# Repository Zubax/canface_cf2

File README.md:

# Babel-Babel

All-in-one hardware solution for developing [Cyphal/CAN](https://opencyphal.org) and DroneCAN devices.

Babel-Babel consists of three devices that are assembled on a single PCB:
2x [Babel](https://zubax.com/babel) USB-CAN adapters and a
[Dronecode probe](https://shop.zubax.com/collections/development-tools/products/dronecode-probe-v2-2-jtag-swd-adapter-usb-uart-adapter-with-dcd-m-cable)
(a generic JTAG/SWD + UART console adapter).

Babel-Babel is connected to the PC with a single USB cable as it contains a built-in USB hub.
It provides the following interfaces for connecting to the device under development:

- CAN 1 (UCANPHY Micro connector)
- CAN 2 (UCANPHY Micro connector)
- SWD and UART (Dronecode Debug connector, medium)
- USB (regular USB A connector)

Along with that, all these interfaces are routed to additional PLS connectors (regular 0.1' single-row pin headers).
These connectors may be used for production testing purposes.

Each Babel can be turned off using the corresponding dip switch.

For technical characteristics, please refer to [requirements document](/docs/requirements.md).

## Standalone debug tool

When the device is used as a standalone debug tool (when the pin headers are not used),
Babel-Babel is constructed using a "novel approach" often called oreo-construction.
This approach eliminates the need for having separate housing,
reliably protecting all the electronics inside the device
while also providing a possibility to deposit some explanatory notes on the top surface of the device
(like the purpose of connectors, pinouts, etc.) without any additional technological processes,
which allows Babel-Babel to be a relatively self-documenting device.

## Production flashing tool

To use Babel-Babel as a production flashing and testing tool, an adapter PCB should be designed.
In general, such PCB should have PBS connectors for Babel-Babel on one side and some connectors
for the device under test (usually pogo pins).
Both Babel-Babel and the device under test can then be connected to this adapter PCB and
the flashing and testing routine can be performed.

Although using Babel-Babel for testing requires some preparations,
it still may be beneficial as it greatly reduces the total amount of
wiring and connectors involved in the production testing routine.
This, in turn, makes the process faster, more reliable, and less painstaking.

The [Mitochondrik-LV](https://zubax.com/mitochondrik-lv) evaluation board is a good example.
To eliminate additional adapter PCBs, the evaluation board is designed to host Babel-Babel directly:

## Manufacturing instructions

For details on the manufacturing process of the device, check the
instructions at [manufacturing document](/docs/manufacturing.md).

## Release notes

Newest entries at the top.

### v1.3 (2025)

* Flip the two rest switches.
* Replaced obsolete part:

| Original | Alternative |
| -------- | ----------- |
| NS5B1G385DTT1G | 74AHC1G66GV,125 |

### v1.2.2 (2023)

* Added alternative part:

| Original | Alternative |
| -------- | ----------- |
| 74LVC2T45DC,125 | 74LVC2T45DC-Q100H |

### v1.2.1 (2023)

* Replaced Parts A, C, and D (spacer) PCBs with 3D.
* Added the Zubax logo to the enclosure PCB.

### v1.2 (2023)

* Fixed silkscreen labels and BOM inconsistencies.
* Replaced references to UAVCAN with Cyphal/CAN.

### v1.1 (2023)

* CAN VDD pulled high with resistor.
* Bootloader switch added to DCP with added pulup resistor.
* CAN VBUS voltage measurement implemented.

### v1.0 (2021)

The original version.

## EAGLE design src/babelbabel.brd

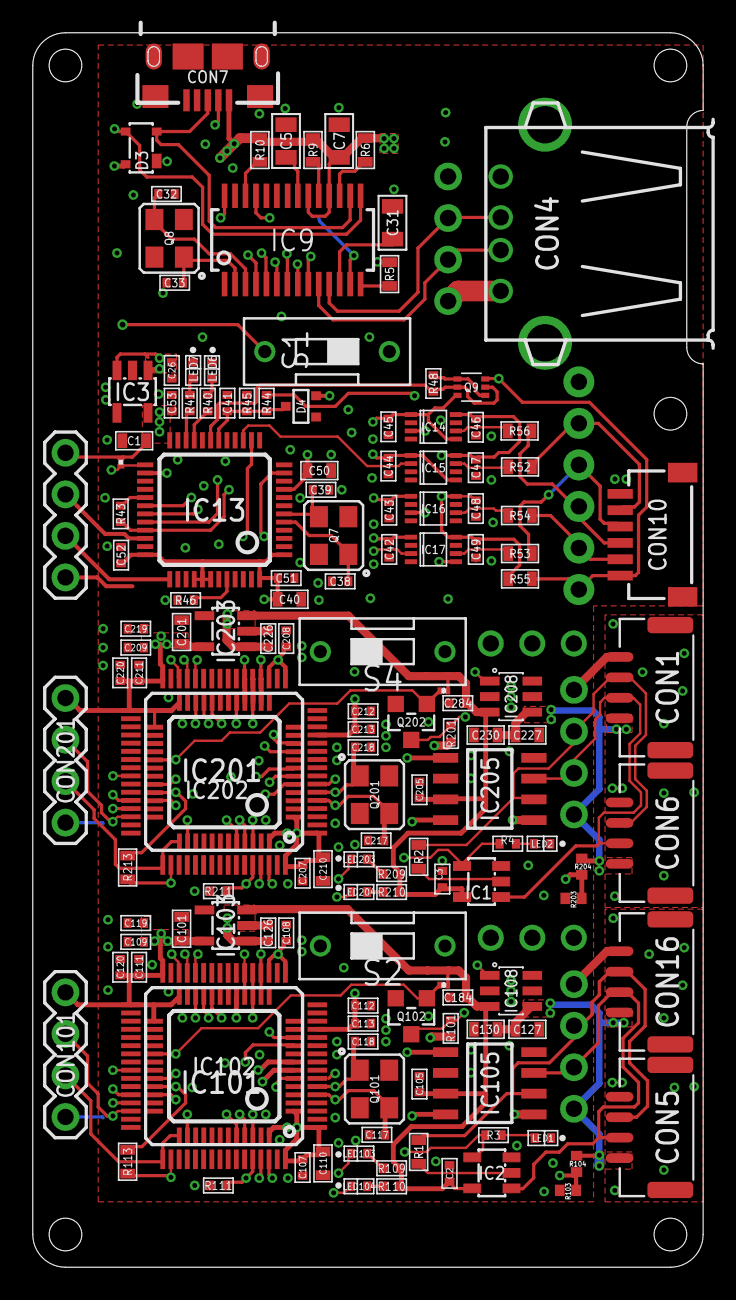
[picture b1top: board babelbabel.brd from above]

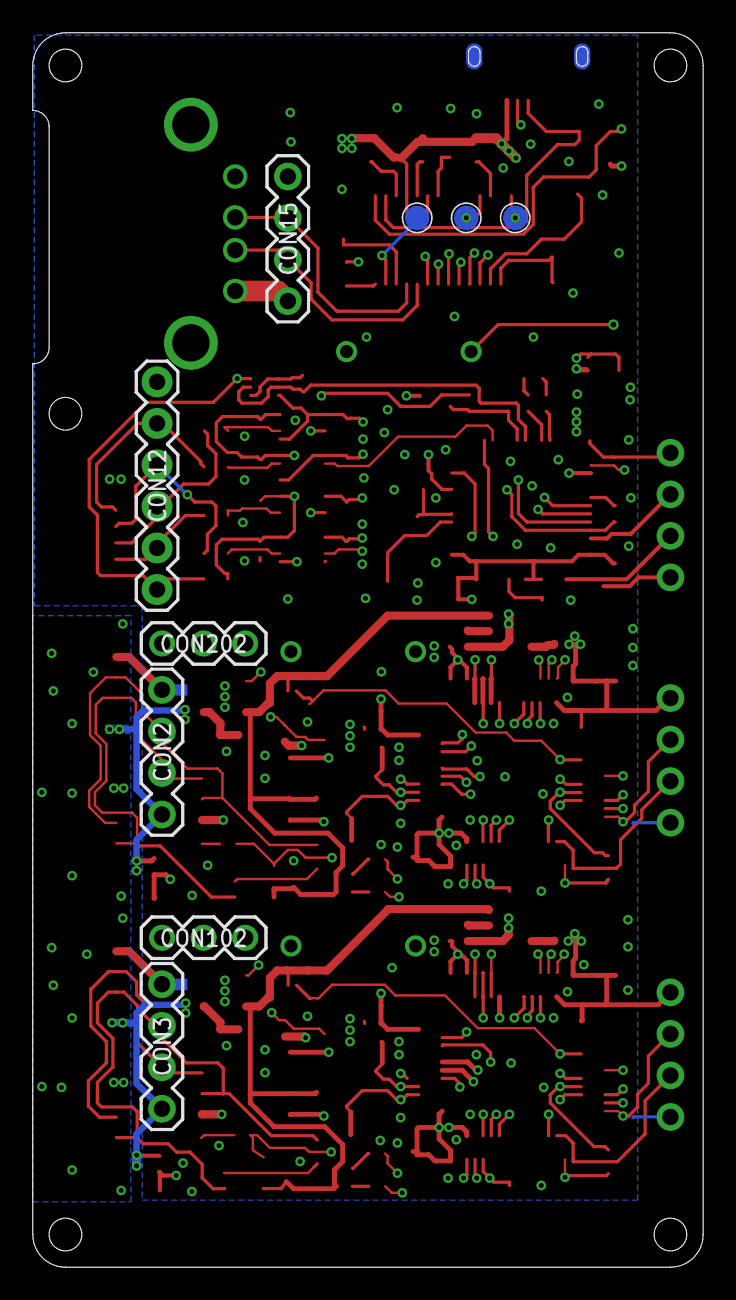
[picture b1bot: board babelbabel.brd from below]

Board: 4 copper layers, 41.0 x 75.5 mm, 156 parts (11 on the bottom side), 106 nets.

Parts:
C1, C40, C50, C101, C110, C127, C130, C201, C210, C227, C230: 4.7uF; C0603
C2, C3, C41, C42, C43, C44, C45, C46, C47, C48, C49, C51, C52, C53, C105, C107, C108, C184, C205, C207, C208, C284: 0.1uF; C0402
C5, C7, C31: 10uF; C0805
C26, C112, C119, C120, C126, C212, C219, C220, C226: 1uF; C0402
C32, C33, C117, C118, C217, C218: 20pF; C0402
C38, C39: 10pF; C0402
C109, C111, C113, C209, C211, C213: 10nF; C0402
CON1, CON5, CON6, CON16: CON-4P-TABS-JST_GH-RA; JST_GH-4P-RA
CON2, CON3, CON11, CON15, CON101, CON201: PINHEAD_1X04-2.54; 1X04-PTH-2.54
CON4: USB-AA-PTH; USB-A-F-PTH
CON7: USB-1; MICRO_USB_PEGS
CON10: CON-6P-SM06B; SM06B
CON12: PINHEAD_1X06-2.54; 1X06-PTH-2.54
CON102, CON202: PINHEAD_1X03-2.54; 1X03-PTH-2.54
D3: PRTR5V0U2X; SOT143B
D4: BAT54SWT1G; SC70
IC1, IC2: NS5B1G385; SOT23-5L
IC3, IC103, IC203: AP2127-3.3; SOT23-5
IC9: FE1.1S; SSOP-28
IC13: STM32F103CBT7; LQFP48
IC14, IC15, IC16, IC17: 74LVC2T45; VSSOP8
IC101, IC201: STM32F373CBT6-LQFP48; LQFP48
IC102, IC202: STM32F373RCT6; TQFP64
IC105, IC205: TJA1051-SO8; SOIC8
IC108, IC208: TPD3S014DBVR-SOT23-6; SOT26
J1, J2: CONNECTION-SMD; CONNECTION
LED1, LED2, LED6, LED7, LED103, LED104, LED203, LED204: LED-0402; LED0402
PAD1, PAD2, PAD4: PAD-S_2X2; 2х2
Q7: 8MHz; OSCILLATOR-3.2X2.5-4P
Q8: 12MHz; OSCILLATOR-3.2X2.5-4P
Q9: NTZD3152PT1G; SOT-563
Q101, Q201: 16MHz; OSCILLATOR-3.2X2.5-4P
Q102, Q202: 2N7002; SOT23
R1, R2, R52, R53, R54, R55, R56: 120R; R0603
R3, R4, R40, R41, R109, R110, R209, R210: 1K; R0402
R5: 2.7K; R0603
R6, R9, R10: 100K; R0603
R8, R102, R202: 10k; R0201
R43: 1K5; R0402
R44: 4K7; R0402
R45, R46, R48, R101, R111, R201, R211: 10K; R0402
R103, R104, R203, R204: 10k; R0402
R113, R213: 1K5; R0603
S1, S2, S4: DS01-STRAIGHT; DS-01

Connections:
BABEL1:BOOT0: IC101.44, IC102.60, R111.2
BABEL1:CAN_COMM: IC101.22, IC102.30, LED104.C
BABEL1:CAN_RX: IC101.45, IC102.61, IC105.4
BABEL1:CAN_STATUS: IC101.21, IC102.29, LED103.C
BABEL1:CAN_TX: IC101.46, IC102.62, IC105.1
BABEL1:CAN_VDD_EN: IC101.29, IC102.41, Q102.1, R102.1
BABEL1:N$1: IC108.1, Q102.3, R101.1
BABEL1:N$4: IC101.10, R103.1, R104.2
BABEL1:N$27: LED103.A, R109.1
BABEL1:N$28: LED104.A, R110.1
BABEL1:PA4: CON102.3, IC101.14, IC102.20
BABEL1:PA5: CON102.2, IC101.15, IC102.21
BABEL1:PA6: CON102.1, IC101.16, IC102.22
BABEL1:PF0: C117.2, IC101.5, IC102.5, Q101.3
BABEL1:PF1: C118.2, IC101.6, IC102.6, Q101.1
BABEL1:SWCLK: CON101.2, IC101.37, IC102.49
BABEL1:SWDIO: CON101.3, IC101.34, IC102.46
BABEL1:USB_PU: IC101.38, IC102.50, R113.2
BABEL1:VDD_3V3: C101.2, C107.1, C108.1, C109.2, C110.1, C111.2, C112.2, C113.2, C119.2, C120.2, CON101.4, IC101.1, IC101.9, IC101.17, IC101.24, IC101.25, IC101.48, IC102.1, IC102.13, IC102.17, IC102.19, IC102.32, IC102.33, IC102.64, IC103.5, IC105.5, R101.2
BABEL1_RST: IC101.7, IC102.7, S2.1
BABEL1_RST1: IC201.7, IC202.7, S4.1
BABEL1_TERM: IC2.4, IC101.20, IC102.28, R3.2
BABEL1_USB_N: IC9.4, IC101.32, IC102.44
BABEL1_USB_P: IC9.5, IC101.33, IC102.45, R113.1
BABEL2:BOOT0: IC201.44, IC202.60, R211.2
BABEL2:CAN_COMM: IC201.22, IC202.30, LED204.C
BABEL2:CAN_RX: IC201.45, IC202.61, IC205.4
BABEL2:CAN_STATUS: IC201.21, IC202.29, LED203.C
BABEL2:CAN_TX: IC201.46, IC202.62, IC205.1
BABEL2:CAN_VDD_EN: IC201.29, IC202.41, Q202.1, R202.1
BABEL2:N$1: IC208.1, Q202.3, R201.1
BABEL2:N$4: IC201.10, R203.1, R204.2
BABEL2:N$27: LED203.A, R209.1
BABEL2:N$28: LED204.A, R210.1
BABEL2:PA4: CON202.3, IC201.14, IC202.20
BABEL2:PA5: CON202.2, IC201.15, IC202.21
BABEL2:PA6: CON202.1, IC201.16, IC202.22
BABEL2:PF0: C217.2, IC201.5, IC202.5, Q201.3
BABEL2:PF1: C218.2, IC201.6, IC202.6, Q201.1
BABEL2:SWCLK: CON201.2, IC201.37, IC202.49
BABEL2:SWDIO: CON201.3, IC201.34, IC202.46
BABEL2:USB_PU: IC201.38, IC202.50, R213.2
BABEL2:VDD_3V3: C201.2, C207.1, C208.1, C209.2, C210.1, C211.2, C212.2, C213.2, C219.2, C220.2, CON201.4, IC201.1, IC201.9, IC201.17, IC201.24, IC201.25, IC201.48, IC202.1, IC202.13, IC202.17, IC202.19, IC202.32, IC202.33, IC202.64, IC203.5, IC205.5, R201.2
BABEL2_TERM: IC1.4, IC201.20, IC202.28, R4.2
BABEL2_USB_N: IC9.6, IC201.32, IC202.44
BABEL2_USB_P: IC9.7, IC201.33, IC202.45, R213.1
CAN1_VDD: C127.2, C130.2, CON3.1, CON5.1, CON16.1, IC108.4, R104.1
CAN1_VDD1: C227.2, C230.2, CON1.1, CON2.1, CON6.1, IC208.4, R204.1
CANH1: CON3.2, CON5.2, CON16.2, IC2.1, IC105.7
CANH2: CON1.2, CON2.2, CON6.2, IC1.1, IC205.7
CANL1: CON3.3, CON5.3, CON16.3, IC105.6, R1.2
CANL2: CON1.3, CON2.3, CON6.3, IC205.6, R2.2
CAN_L: IC2.2, R1.1
CONSOLE_RX: CON10.3, CON12.3, R56.2
CONSOLE_TX: CON10.2, CON12.2, R54.2
DCP_DM: IC9.8, IC13.32
DCP_DP: IC9.9, IC13.33, R43.2
DUT_DM: CON4.D-, CON15.2, IC9.10
DUT_DP: CON4.D+, CON15.3, IC9.11
GND: C1.1, C2.1, C3.1, C5.1, C7.1, C26.1, C31.1, C32.1, C33.1, C38.2, C39.2, C40.2, C41.1, C42.2, C43.2, C44.2, C45.2, C46.1, C47.1, C48.1, C49.1, C50.1, C51.2, C52.1, C53.2, C101.1, C105.1, C107.2, C108.2, C109.1, C110.2, C111.1, C112.1, C113.1, C117.1, C118.1, C119.1, C120.1, C126.1, C127.1, C130.1, C184.2, C201.1, C205.1, C207.2, C208.2, C209.1, C210.2, C211.1, C212.1, C213.1, C217.1, C218.1, C219.1, C220.1, C226.1, C227.1, C230.1, C284.2, CON4.GND, CON7.GND, CON7.GND1, CON7.GND2, CON7.GND3, CON7.GND4, CON7.P$1, CON7.P$2, CON7.P$3, CON7.P$4, CON10.6, CON10.G1, CON10.G2, CON11.1, CON12.6, CON15.4, CON101.1, CON201.1, D3.1, D4.1, IC1.3, IC2.3, IC3.2, IC9.1, IC13.8, IC13.23, IC13.35, IC14.2, IC14.4, IC14.7, IC15.4, IC16.4, IC16.5, IC17.2, IC17.4, IC17.7, IC101.8, IC101.23, IC101.47, IC102.12, IC102.31, IC102.63, IC103.2, IC105.2, IC105.8, IC108.2, IC201.8, IC201.23, IC201.47, IC202.12, IC202.31, IC202.63, IC203.2, IC205.2, IC205.8, IC208.2, J1.P$1, J2.P$1, LED1.C, LED2.C, LED6.C, LED7.C, Q7.2, Q7.4, Q8.2, Q8.4, Q101.2, Q101.4, Q102.2, Q201.2, Q201.4, Q202.2, R5.1, R45.1, R46.2, R103.2, R111.1, R203.2, R211.1, S1.1, S2.10, S4.10
GNDD: CON1.4, CON1.M$0, CON1.M$1, CON2.4, CON3.4, CON5.4, CON5.M$0, CON5.M$1, CON6.4, CON6.M$0, CON6.M$1, CON16.4, CON16.M$0, CON16.M$1, J1.P$2, J2.P$2
IRXD: IC13.31, IC16.3
ITCK: IC13.15, IC15.2
ITMS: IC13.14, IC17.3
ITMS_DIR: IC13.11, IC17.5
ITXD: IC13.30, IC14.3
LED1: IC13.21, R40.2
LED2: IC13.22, R41.2
unnamed: LED1.A, R3.1
unnamed: IC1.2, R2.1
unnamed: LED2.A, R4.1
unnamed: C31.2, IC9.12
unnamed: IC9.14, R5.2
unnamed: C33.2, IC9.2, Q8.1
unnamed: C32.2, IC9.3, Q8.3
unnamed: CON7.D+, D3.2, IC9.16
unnamed: CON7.D-, D3.3, IC9.15
unnamed: IC9.26, R10.1
unnamed: C5.2, IC9.21
unnamed: IC9.17, R6.1
unnamed: IC9.19, R9.1
unnamed: IC9.25, PAD4.P$1
unnamed: IC9.13, PAD1.P$1
unnamed: IC9.28, PAD2.P$1
unnamed: C38.1, IC13.5, Q7.1
unnamed: C39.1, IC13.6, Q7.3
unnamed: LED6.A, R40.1
unnamed: LED7.A, R41.1
unnamed: IC13.29, R43.1
unnamed: IC13.44, R46.1
unnamed: Q9.1, Q9.4, R48.1
PWR_BR: IC13.19, Q9.2, Q9.5, R48.2
SWCLK: CON11.2, IC13.37
SWDIO: CON11.3, IC13.34
SWITCH: IC13.25, R8.1, S1.10
TCK: CON10.5, CON12.5, R52.2
TMS: CON10.4, CON12.4, R53.2
TPWR: CON10.1, CON12.1, Q9.6, R44.2, R55.2
VBUS3: C41.2, D4.3, IC13.18, R44.1, R45.2
VDD_3V3: C1.2, C40.1, C42.1, C43.1, C44.1, C45.1, C50.2, C51.1, C52.2, C53.1, CON11.4, D4.2, IC3.5, IC13.1, IC13.9, IC13.24, IC13.36, IC13.40, IC13.41, IC13.42, IC13.48, IC14.1, IC14.5, IC15.1, IC15.5, IC16.1, IC17.1, Q9.3, R8.2
VDD_5V: C2.2, C3.2, C7.2, C26.2, C105.2, C126.2, C184.1, C205.2, C226.2, C284.1, CON4.VBUS, CON7.VBUS, CON15.1, D3.4, IC1.5, IC2.5, IC3.1, IC3.3, IC9.18, IC9.20, IC13.26, IC103.1, IC103.3, IC105.3, IC108.3, IC203.1, IC203.3, IC205.3, IC208.3, R6.2, R9.2, R10.2, R102.2, R109.2, R110.2, R202.2, R209.2, R210.2
XRXD: IC16.6, R54.1
XTCK: IC15.7, R52.1
XTMS: IC17.6, R53.1
XTPWR: C46.2, C47.2, C48.2, C49.2, IC14.8, IC15.8, IC16.8, IC17.8, R55.1
XTXD: IC14.6, R56.1

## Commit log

2020-12-21 initial import
2020-12-21 organisation
2020-12-22 Routing seems done
2020-12-23 excessive DCP nets removed
2020-12-23 PLS connector for DCP connector rotated 180 degrees to match DCP connector
2020-12-25 SSOP28 footprint update
2020-12-25 Silkscreen fix
2020-12-25 All doubtful issues resolved
2020-12-25 CAN transciever replaced
2020-12-25 Babel part attributes added
2020-12-25 Massive attribute update
2020-12-25 BOM improvement
2020-12-28 UAVCAN PLS connectors fixed
2020-12-28 Minor tweaks
2020-12-28 all base features are now locked
2021-01-05 pictures added
2021-01-06 Analog switch added as alternative to mechanical switch for switching termination resistor in babel
2021-01-06 DRC fixes
2021-01-06 3d model updates
2021-01-08 manufacturing instructions
2021-01-08 flashing connectors pinout added
2021-01-13 Pictures updated
2021-01-14 Correct the docs (no substantial changes, mostly grammar and formatting)
2021-01-14 Add links to Babel and DCP
2021-01-15 source files consistency fix
2021-01-15 Revert "Delete part B.brd"
    This reverts commit 4a45031003260e5b2cc94cb50fce3c8d96386cdc.
2021-01-15 Revert "source files consistency fix"
    This reverts commit 015ba0159d9c48fa3345c98b8ff1ca9c9c6bfb7d.
2021-01-15 fixes for https://github.com/Zubax/Babel-Babel/pull/1
2021-01-15 Fixes for release preparation v0.1 (#3)
    * source files consistency fix
    * Delete part B.brd
    * Revert "Delete part B.brd"
    This reverts commit 4a45031003260e5b2cc94cb50fce3c8d96386cdc.
    * Revert "source files consistency fix"
    This reverts commit 015ba0159d9c48fa3345c98b8ff1ca9c9c6bfb7d.
2021-01-15 Correct the docs (no substantial changes, mostly grammar and formatting) (#1)
    * Correct the docs (no substantial changes, mostly grammar and formatting)
    * Add links to Babel and DCP
    * Fixes for release preparation v0.1 (#3)
    * source files consistency fix
    * Delete part B.brd
    * Revert "Delete part B.brd"
2021-01-21 Attribute updates for manufacturability
2021-01-29 Attribute updates for manufacturability (#4)
2021-04-19 Update blow_scheme.svg (#7)
    Fixes #5
2021-07-30 connected Vref to VDD, fixes #10
2021-07-30 connected Vref to VDD, fixes #10 (#11)
2021-07-30 removed mosfet Q2 from both babel, fixes #6
2021-07-30 removed Q2
2021-07-30 minor routing improvement
2021-08-02 cutout for DCP LED
2021-08-03 fixes #6
2021-08-04 trace width fixes #6
2021-08-04 ratnest fix, clean DRC
2021-08-04 Fixed mosfet Q2 from both babel, fixes #6 (#12)
    * removed mosfet Q2 from both babel, fixes #6
    * removed Q2
    * minor routing improvement
    * cutout for DCP LED
    * fixes #6
    * trace width fixes #6
2021-08-05 removed assembly variant mechanical terminator fixes #13
2021-08-05 removed assembly variant Electronic terminator and components that were not in use, now we have default variant
2021-08-13 Removed unnecessary assembly variant "mechanical terminator" fixes #13 (#15)
    * removed mosfet Q2 from both babel, fixes #6
    * removed Q2
    * minor routing improvement
    * cutout for DCP LED
    * fixes #6
    * trace width fixes #6
2021-08-13 fixes switch label
2021-08-13 fixes switch label (#17)
2021-08-13 resolved board not opening issue
2021-08-13 Revert "Fixed mosfet Q2 from both babel, fixes #6 (#12)"
    This reverts commit d39d7e4d46531cf5480a8d684ba2b4b43b92db19.
2021-08-13 fixed mosfet Q2
2021-08-13 fixed switch label in top board
2021-08-13 removed unnecessary assembly variant
2021-08-13 Redoing past changes and new fixes (#20)
    * fixed mosfet Q2
    * fixed switch label in top board
    * removed unnecessary assembly variant
2021-08-13 changed footprint CON4
2021-08-13 fixed wrong USB connection
2021-08-13 changed footprint CON4 (#21)
    * changed footprint CON4
    * fixed wrong USB connection
2021-08-13 repo directories restructured
2021-08-16 First release (#22)
    * repo directories restructured
    * Update README.md
    * Update README.md
    * Update manufacturing.md
2021-10-07 64 pin swaped with 48
2021-10-08 64 pin swaped with 48 (#23)
2021-10-22 DCP switch pulled high
2021-10-22 Added changelog for V1.1
2021-11-02 manufacturing doc edited
2021-11-02 manufacturing doc updated and DCP part can be updated suitable to babel in next release, for now it forwards to original DCP flashing page
2022-06-24 manufacturing doc edited (#26)
    * manufacturing doc updated and DCP part can be updated suitable to babel in next release, for now it forwards to original DCP flashing page
2023-02-01 CAN bus voltage measurement implemented #29
2023-02-01 CAN_VDD_EN pulled up to 5v #28
2023-02-01 #31 #30 #9
2023-02-01 ready for review
2023-02-01 minor changes
2023-02-01 version text added
2023-02-02 CAN bus voltage measurement implemented #29 (#32)
    * CAN bus voltage measurement implemented #29
    * CAN_VDD_EN pulled up to 5v #28
    * #31 #30 #9
    * ready for review
    * minor changes
    * version text added
2023-02-03 rename board file
2023-02-03 rename board file (#33)
2023-03-23 manufacturer fix, no electrical changes were done
2023-03-23 manufacturer fix, no electrical changes were done (#34)
2023-04-17 Update the silkscreen labels and approve ERC warnings
2023-04-17 Update the docs
2023-04-17 Swap the boot selector labels
2023-04-17 v1.2 with fixes (#36)
    Fix #35
    Fix silkscreen labels
    Actualize the docs
2023-07-14 added alternative spacers
    Alternative spacers for parts A & C - assembly with parts B & D remain the same
2023-07-21 modified
2023-07-25 updated 3D part A
    modified part A spacer
2023-07-25 updated manufacturing instructions
2023-07-25 added screw length
2023-07-27 Add Zubax logo to enclosure
2023-07-27 Add Zubax logo to enclosure (#39)
2023-07-27 bringing Kasim's changes to this branch
2023-07-27 renamed to enclosure
2023-07-27 Revert "renamed to enclosure"
    This reverts commit 143be9e5a0b523cffdd5703daeeaaacab54ca0e7.
2023-07-27 Revert "Revert "renamed to enclosure""
    This reverts commit 7f0c3808ede02c5e2af3eaf84a6e78f6d0782537.
2023-08-01 updated changelog
2023-08-01 renamed back to part B
    to remove conflict
2023-08-01 new spacers & manufacturing instructions (#37)
    Alternative spacers for parts A & C - assembly with parts B & D remain
    the same
    [BABBAB-1]
    [BABBAB-1]:
    https://zubax.atlassian.net/browse/BABBAB-1?atlOrigin=eyJpIjoiNWRkNTljNzYxNjVmNDY3MDlhMDU5Y2ZhYzA5YTRkZjUiLCJwIjoiZ2l0aHViLWNvbS1KU1cifQ
2023-08-01 renamed part B to enclosure
2023-08-01 renamed part B to enclosure (#40)
2023-08-01 updated changelog for clarity
2023-08-01 updated changelog for clarity (#41)
2023-08-30 added manufacturing note & alternative part
2023-08-31 added manufacturing note & alternative part (#42)
    will release the new manufacturing pack after this is merged
2023-09-06 flip the rest switches
2023-09-07 update change log
2023-09-07 resolve conflict
2023-09-07 flip the rest switches (#44)
2025-01-15 part number update & v1.3 mfgpack release
    NS5B1G385DTT1G is obsolete
    74AHC1G66GV,125 is a direct replacement
    updated manufacturing pack
2025-01-23 part number update & v1.3 mfgpack release (#47)
    NS5B1G385DTT1G is obsolete
    74AHC1G66GV,125 is a direct replacement
    will update manufacturing pack
    <!-- This is an auto-generated comment: release notes by coderabbit.ai
    -->
    ## Summary by CodeRabbit
2025-05-18 update mfg docs
2026-03-27 new enclosure files
2026-03-27 New enclosure files (#50)
2026-05-07 Fix holes
2026-05-07 Fix holes orientation (#51)
    The last batch had the holes in the wrong orientation, resulting in the
    logo print being on the inside when mounted.
    (There was also a problem with the thickness which had to be 0.8mm
    instead of the standard 1.6mm.)
